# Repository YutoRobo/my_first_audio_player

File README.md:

# my_first_audio_player
## 概要 
PCM1793を用いたDAC基板です。I2S信号を送ることで24bit音源を流せるはずです。

## 回路図

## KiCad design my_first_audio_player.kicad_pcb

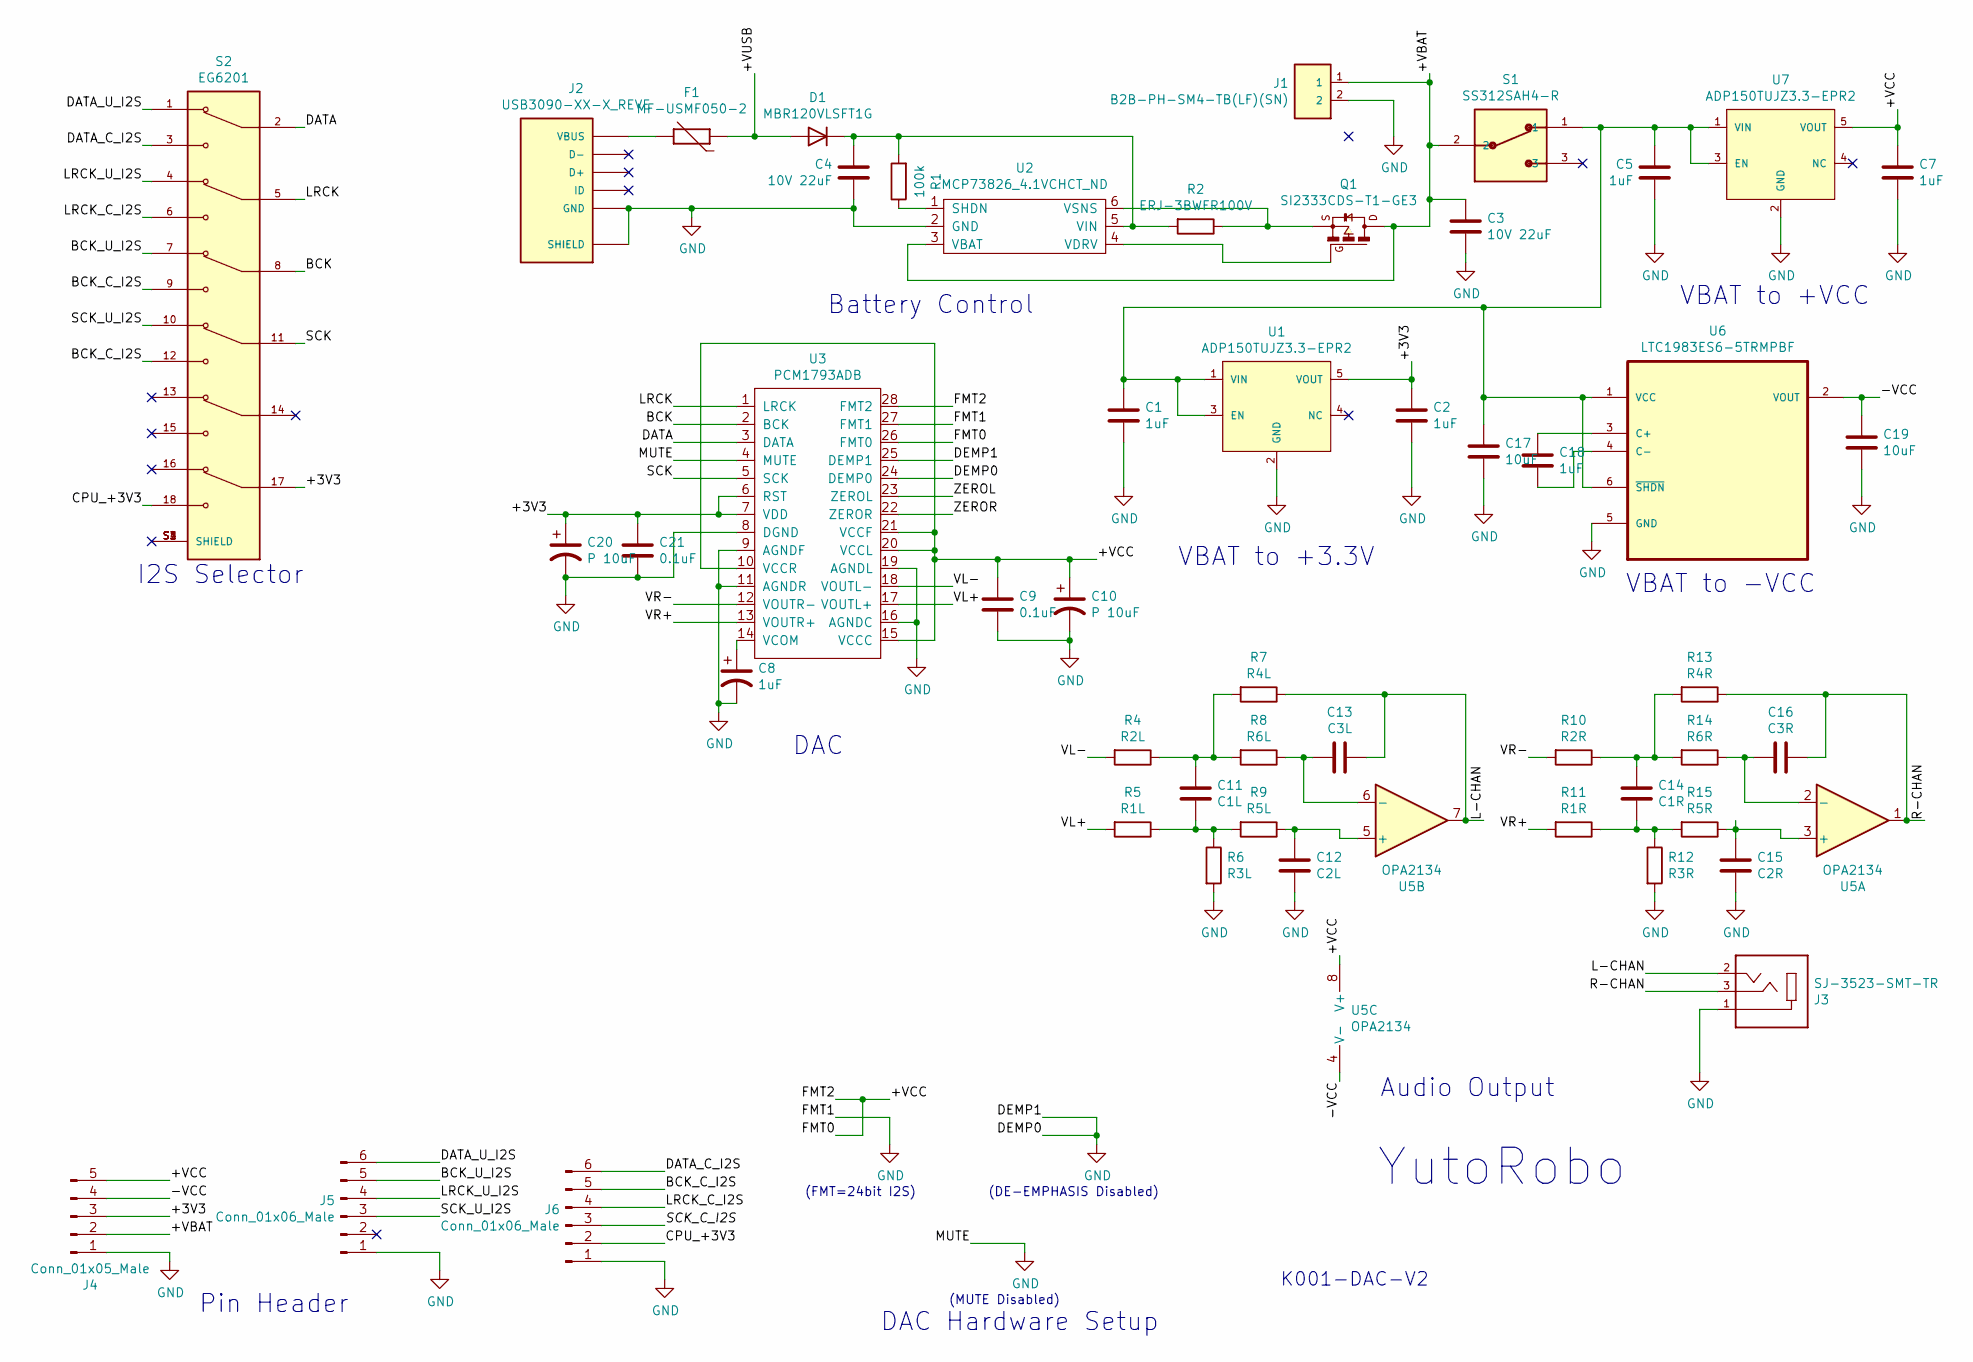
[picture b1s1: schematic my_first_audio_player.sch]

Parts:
C1, C2, C5, C7, C8, C18: 1uF; C_0805_2012Metric
C3, C4: 10V 22uF; C_0805_2012Metric
C9, C21: 0.1uF; C_0805_2012Metric
C10, C20: P 10uF; CAPAE660X800N
C11: C1L; C_0805_2012Metric
C12: C2L; C_0805_2012Metric
C13: C3L; C_0805_2012Metric
C14: C1R; C_0805_2012Metric
C15: C2R; C_0805_2012Metric
C16: C3R; C_0805_2012Metric
C17, C19: 10uF; C_0805_2012Metric
D1: MBR120VLSFT1G; SODFL3616X98N_pin12
F1: MF-USMF050-2; FUSER_MF-USMF050-2; PARTREV R
J1: B2B-PH-SM4-TB(LF)(SN); JST_B2B-PH-SM4-TB(LF)(SN)
J2: USB3090-XX-X_REVE; GCT_USB3090-XX-X_REVE
J3: SJ-3523-SMT-TR; CUI_SJ-3523-SMT-TR
J4: Conn_01x05_Male; PinHeader_1x05_P2.54mm_Vertical
J5, J6: Conn_01x06_Male; PinSocket_1x06_P2.54mm_Vertical
Q1: SI2333CDS-T1-GE3; SOT23
R1: 100k; R_0805_2012Metric
R2: ERJ-3BWFR100V; RESC1608X55N
R4: R2L; R_0805_2012Metric
R5: R1L; R_0805_2012Metric
R6: R3L; R_0805_2012Metric
R7: R4L; R_0805_2012Metric
R8: R6L; R_0805_2012Metric
R9: R5L; R_0805_2012Metric
R10: R2R; R_0805_2012Metric
R11: R1R; R_0805_2012Metric
R12: R3R; R_0805_2012Metric
R13: R4R; R_0805_2012Metric
R14: R6R; R_0805_2012Metric
R15: R5R; R_0805_2012Metric
S1: SS312SAH4-R; SW_SS312SAH4-R
S2: EG6201; SW_EG6201; PARTREV B
U1, U7: ADP150TUJZ3.3-EPR2; Analog_Devices-ADP151TUJZ3.3-EPR2-Level_A
U2: MCP73826_4.1VCHCT_ND; SOT95P280X145-6N
U3: PCM1793ADB; SOP65P780X200-28N
U5: OPA2134; SOIC127P599X175-8N
U6: LTC1983ES6-5TRMPBF; SOT95P280X100-6N; MPN LTC1983ES6-5#TRMPBF

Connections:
/+3V3: C2.1, C20.1, C21.1, J4.3, S2.17, U1.5 (VOUT), U3.6 (RST), U3.7 (VDD)
/+VBAT: C3.1, J1.1, J4.2, Q1.3, S1.2, U2.3 (VBAT)
/+VCC: C7.1, C9.1, C10.1, J4.5, U3.10 (VCCR), U3.15 (VCCC), U3.20 (VCCL), U3.21 (VCCF), U3.26 (FMT0), U3.28 (FMT2), U5.8 (V+), U7.5 (VOUT)
/+VUSB: D1.1 (A), F1.1
/-VCC: C19.1, J4.4, U5.4 (V-), U6.2 (VOUT)
/BCK: S2.8, U3.2 (BCK)
/BCK_C_I2S: J6.5, S2.9, S2.12
/BCK_U_I2S: J5.5, S2.7
/CPU_+3V3: J6.2, S2.18
/DATA: S2.2, U3.3 (DATA)
/DATA_C_I2S: J6.6, S2.3
/DATA_U_I2S: J5.6, S2.1
/L-CHAN: C13.1, J3.2, R7.1, U5.7
/LRCK: S2.5, U3.1 (LRCK)
/LRCK_C_I2S: J6.4, S2.6
/LRCK_U_I2S: J5.4, S2.4
/R-CHAN: C16.1, J3.3, R13.1, U5.1
/SCK: S2.11, U3.5 (SCK)
/SCK_C_I2S: J6.3
/SCK_U_I2S: J5.3, S2.10
/VL+: R5.2, U3.17 (VOUTL+)
/VL-: R4.2, U3.18 (VOUTL-)
/VR+: R11.2, U3.13 (VOUTR+)
/VR-: R10.2, U3.12 (VOUTR-)
/ZEROL: U3.23 (ZEROL)
/ZEROR: U3.22 (ZEROR)
GND: C1.2, C2.2, C3.2, C4.2, C5.2, C7.2, C8.2, C9.2, C10.2, C12.2, C15.2, C17.2, C19.2, C20.2, C21.2, J1.2, J2.5 (GND), J2.6 (SHIELD), J2.7 (SHIELD), J2.8 (SHIELD), J2.9 (SHIELD), J3.1, J4.1, J5.1, J6.1, R6.2, R12.2, U1.2 (GND), U2.2 (GND), U3.4 (MUTE), U3.8 (DGND), U3.9 (AGNDF), U3.11 (AGNDR), U3.16 (AGNDC), U3.19 (AGNDL), U3.24 (DEMP0), U3.25 (DEMP1), U3.27 (FMT1), U6.5 (GND), U7.2 (GND)
unnamed: C1.1, C5.1, C17.1, S1.1, U1.1 (VIN), U1.3 (EN), U6.1 (VCC), U6.6 (~SHDN), U7.1 (VIN), U7.3 (EN)
unnamed: C4.1, D1.2 (K), R1.2, R2.2, U2.5 (VIN)
unnamed: C8.1, U3.14 (VCOM)
unnamed: C11.1, R4.1, R7.2, R8.2
unnamed: C11.2, R5.1, R6.1, R9.2
unnamed: C12.1, R9.1, U5.5 (+)
unnamed: C13.2, R8.1, U5.6 (-)
unnamed: C14.1, R10.1, R13.2, R14.2
unnamed: C14.2, R11.1, R12.1, R15.2
unnamed: C15.1, R15.1, U5.3 (+)
unnamed: C16.2, R14.1, U5.2 (-)
unnamed: C18.1, U6.3 (C+)
unnamed: C18.2, U6.4 (C-)
unnamed: F1.2, J2.1 (VBUS)
unnamed: Q1.1, U2.4 (VDRV)
unnamed: Q1.2, R2.1, U2.6 (VSNS)
unnamed: R1.1, U2.1 (SHDN)
unnamed: S2.S1 (SHIELD), S2.S2 (SHIELD), S2.S3 (SHIELD), S2.S4 (SHIELD)

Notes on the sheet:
DAC Hardware Setup
(MUTE Disabled)
(DE-EMPHASIS Disabled)
(FMT=24bit I2S)
DAC
YutoRobo
VBAT to -VCC
K001-DAC-V2
Audio Output
VBAT to +3.3V
Battery Control
VBAT to +VCC
Pin Header
I2S Selector

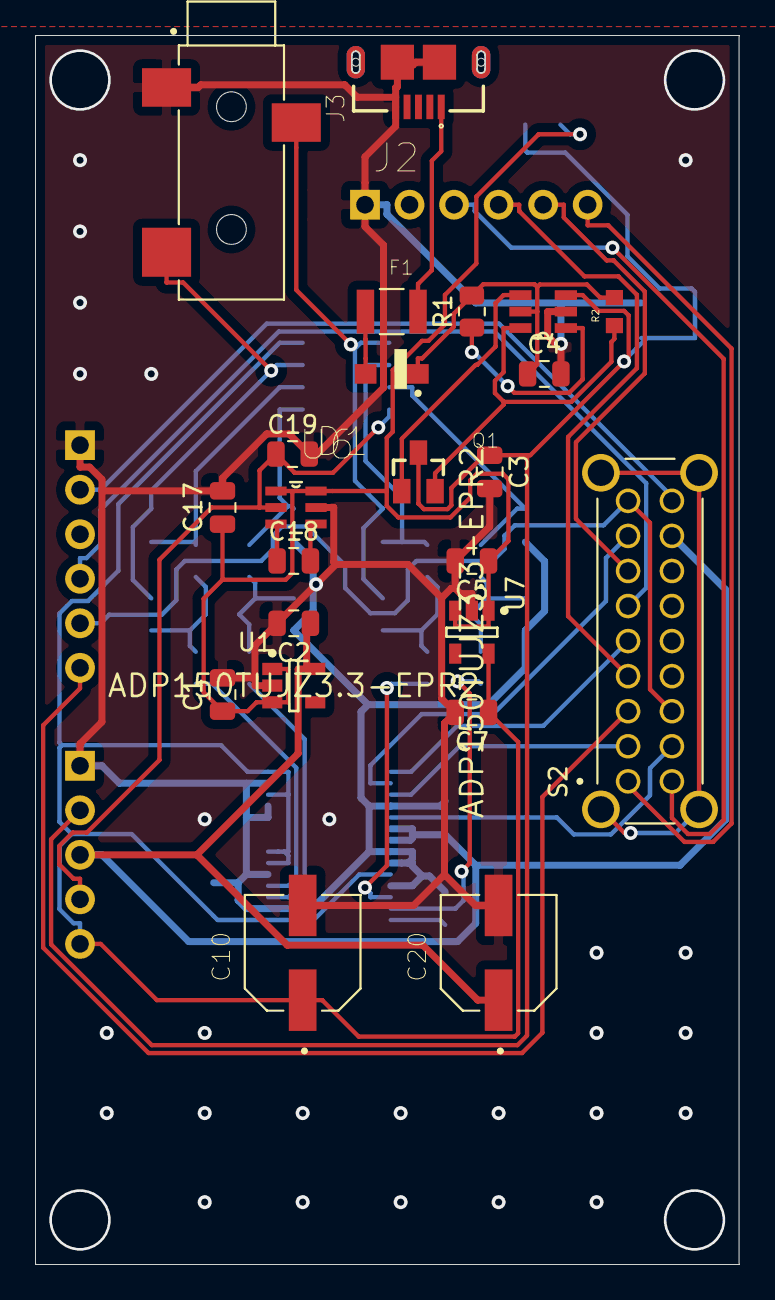
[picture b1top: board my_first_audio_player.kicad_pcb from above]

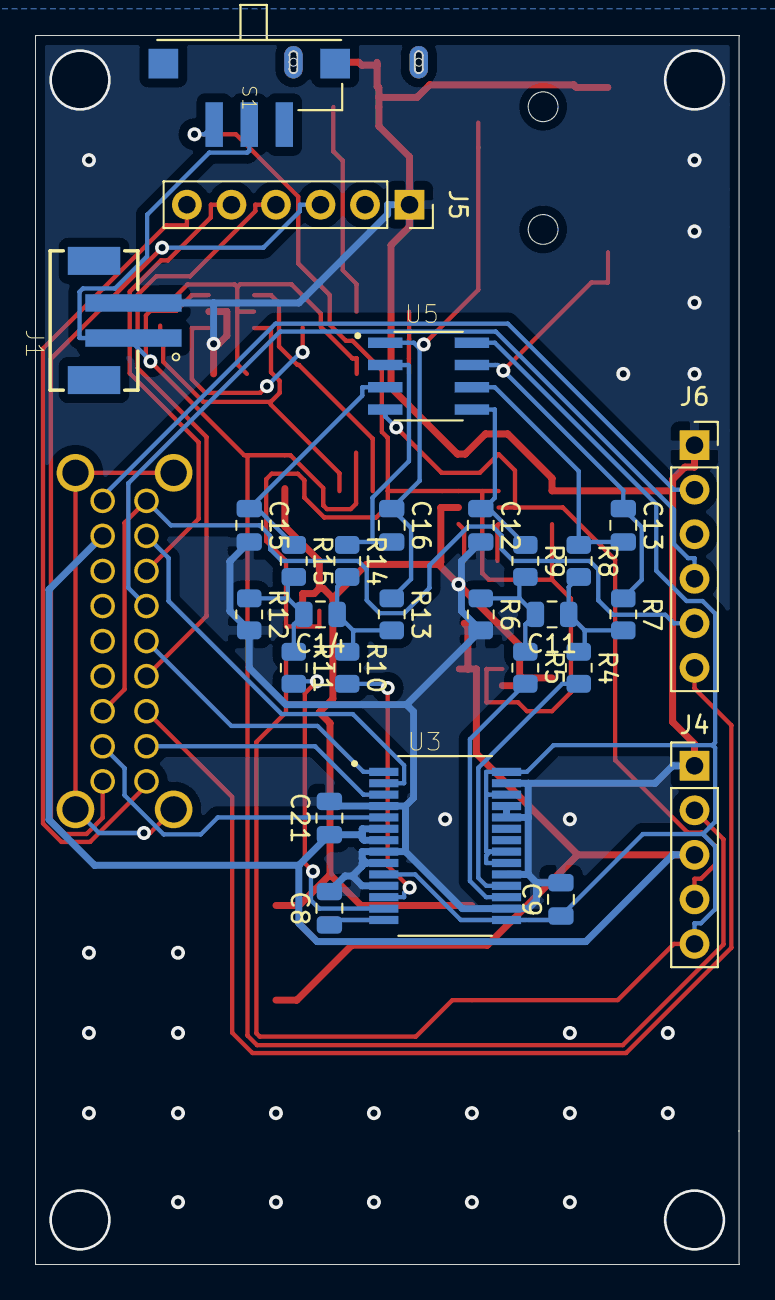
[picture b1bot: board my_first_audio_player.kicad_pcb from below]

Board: 2 copper layers, 40.1 x 70.1 mm, 51 parts (28 on the bottom side), 42 nets.

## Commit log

2021-09-15 [Minor] initial ordered data (develop)
2021-09-15 [Minor] Add image (develop)
2021-09-15 [Minor] A bit fixed on README (develop)
2021-09-16 [Minor] Still not edit Switch, ESP32I2S, PinsocketNumber (develop)
2021-09-16 [Minor] Maybe create ver2 sch (develop)
2021-09-17 [Minor] Before order second version (develop)
2021-12-21 [Minor] 久しぶりの謎コミットなのでバグあるかもしれないです (develop)
